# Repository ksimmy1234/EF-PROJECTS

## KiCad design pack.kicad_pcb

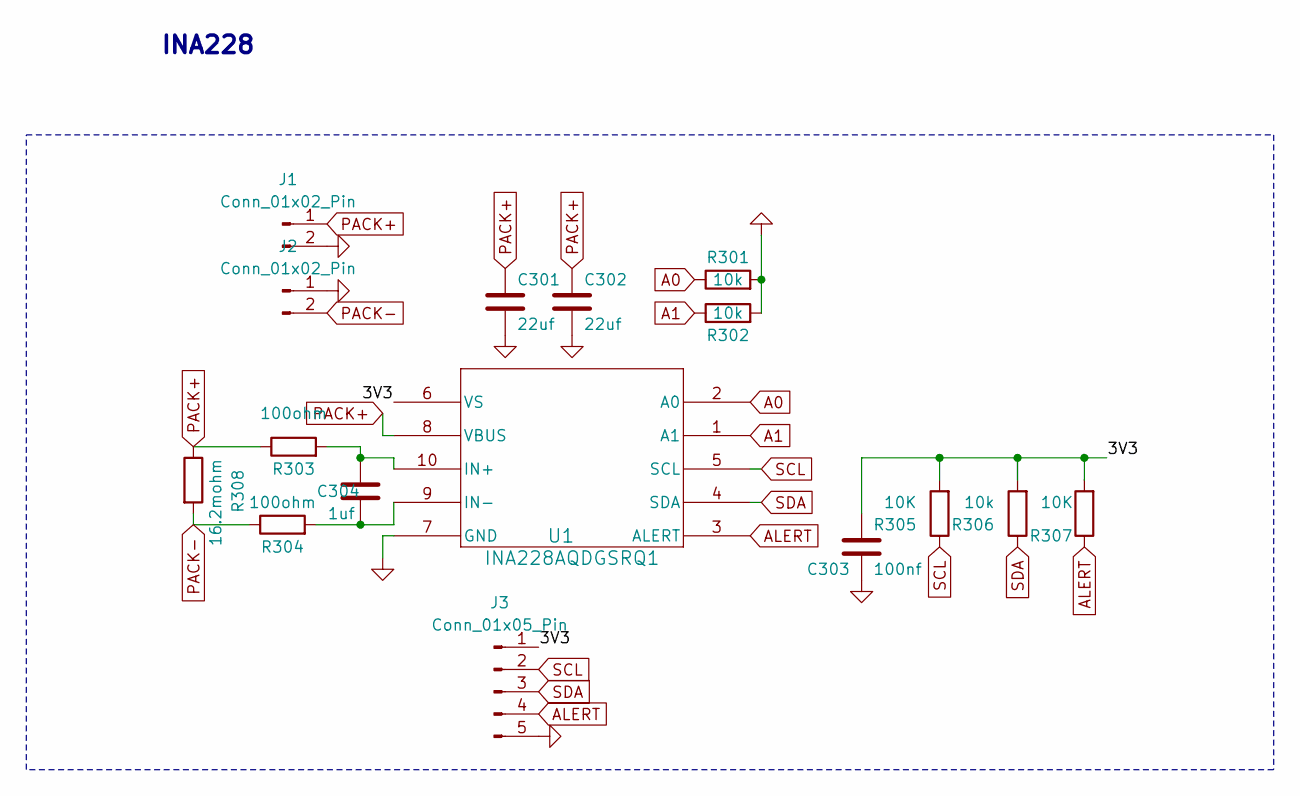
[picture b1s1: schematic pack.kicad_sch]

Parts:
C301, C302: 22uf; C_0603_1608Metric_Pad1.08x0.95mm_HandSolder
C303: 100nf; C_0805_2012Metric_Pad1.18x1.45mm_HandSolder
C304: 1uf; C_0402_1005Metric_Pad0.74x0.62mm_HandSolder
J1, J2: Conn_01x02_Pin; JWT_A3963_1x02_P3.96mm_Vertical
J3: Conn_01x05_Pin; PinHeader_1x05_P1.00mm_Vertical
R301, R302, R306: 10k; R_0603_1608Metric_Pad0.98x0.95mm_HandSolder
R303, R304: 100ohm; R_0603_1608Metric_Pad0.98x0.95mm_HandSolder
R305, R307: 10K; R_0603_1608Metric_Pad0.98x0.95mm_HandSolder
R308: 16.2mohm; R_1210_3225Metric_Pad1.30x2.65mm_HandSolder
U1: INA228AQDGSRQ1; VSSOP-10_3x3mm_P0.5mm

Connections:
/3V3: C303.1, J3.1, R305.2, R306.2, R307.2, U1.6 (VS)
A0: R301.1, U1.2 (A0)
A1: R302.1, U1.1 (A1)
ALERT: J3.4, R307.1, U1.3 (ALERT)
GND: C301.2, C302.2, C303.2, J1.2, J2.1, J3.5, R301.2, R302.2, U1.7 (GND)
unnamed: C304.1, R303.2, U1.10 (IN+)
unnamed: C304.2, R304.2, U1.9 (IN-)
PACK+: C301.1, C302.1, J1.1, R303.1, R308.1, U1.8 (VBUS)
PACK-: J2.2, R304.1, R308.2
SCL: J3.2, R305.1, U1.5 (SCL)
SDA: J3.3, R306.1, U1.4 (SDA)

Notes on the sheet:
INA228

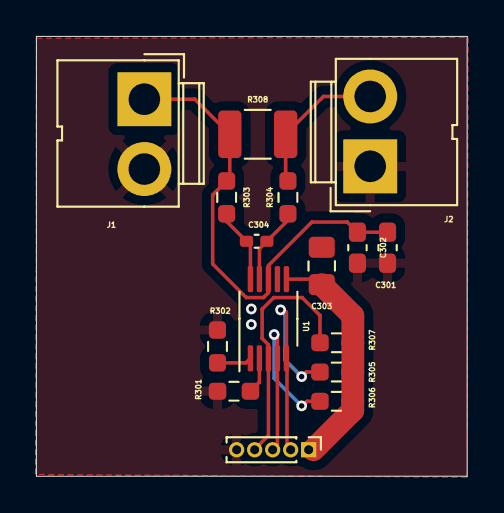
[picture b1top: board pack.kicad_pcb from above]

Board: 2 copper layers, 23.9 x 24.4 mm, 16 parts (0 on the bottom side), 11 nets.
